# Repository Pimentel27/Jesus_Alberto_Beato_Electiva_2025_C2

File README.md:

# Jesus_Alberto_Beato_Electiva_2025_C2

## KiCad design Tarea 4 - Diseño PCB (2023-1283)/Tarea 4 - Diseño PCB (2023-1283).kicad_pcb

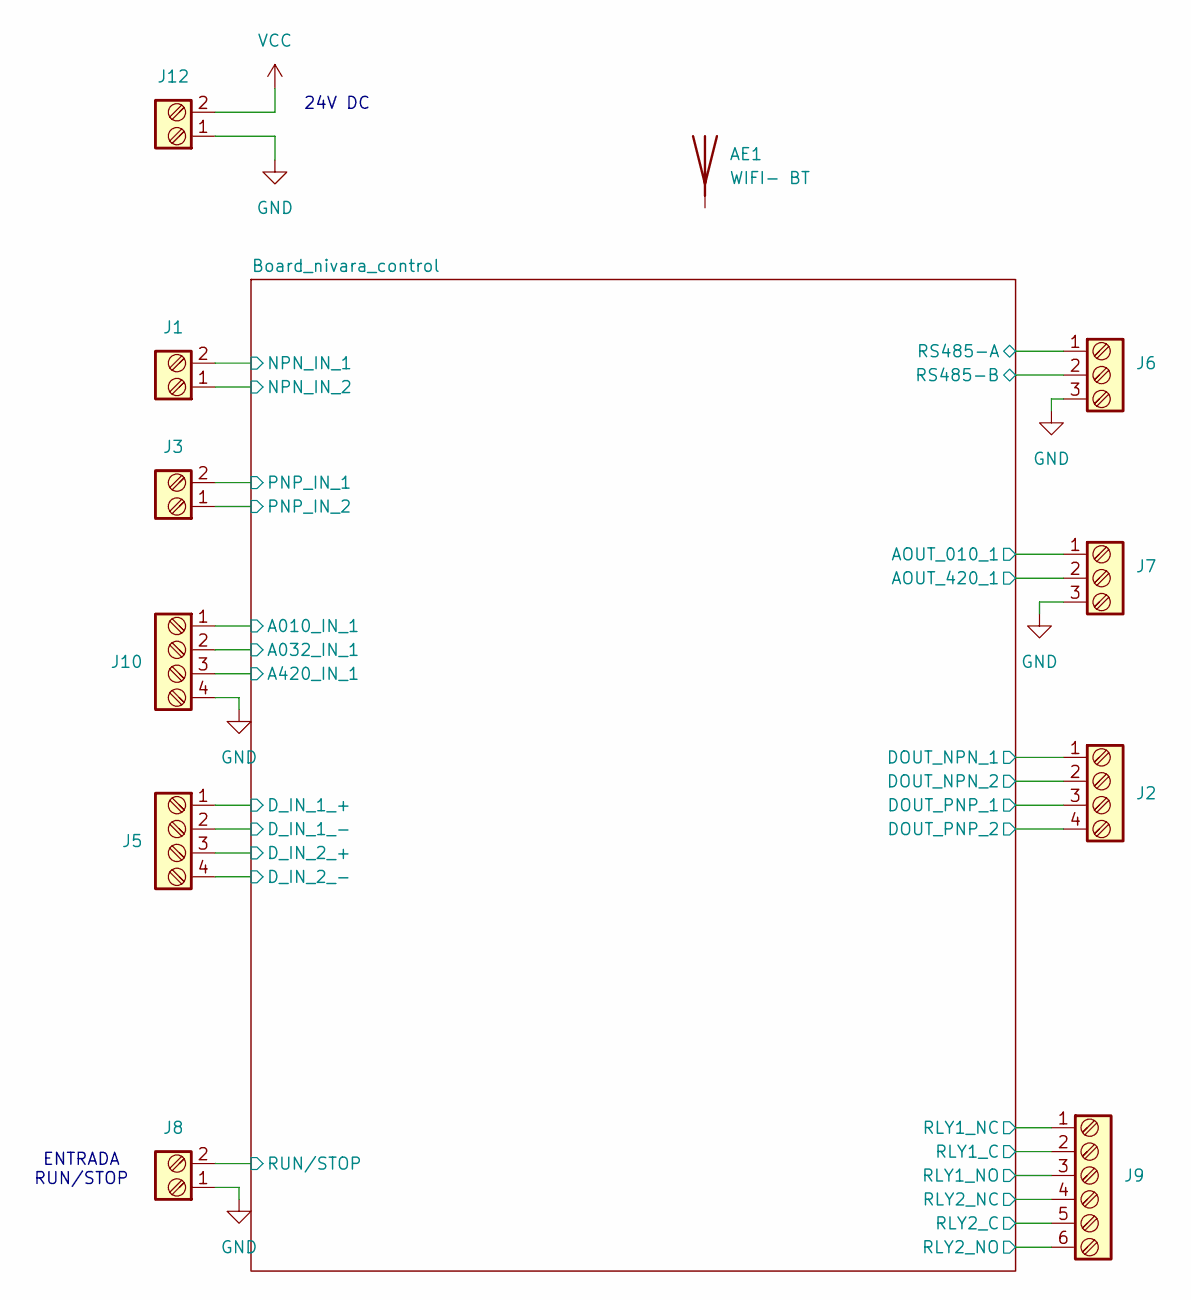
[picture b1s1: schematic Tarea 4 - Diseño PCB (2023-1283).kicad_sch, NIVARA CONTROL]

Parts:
AE1: WIFI- BT
J1, J3, J8, J12: Screw_Terminal_2_P5.00mm; TerminalBlock_Phoenix_PT-1,5-2-5.0-H_1x02_P5.00mm_Horizontal
J2, J5, J10: Screw_Terminal_4_P5.00mm; TerminalBlock_Phoenix_PT-1,5-4-5.0-H_1x04_P5.00mm_Horizontal
J6, J7: Screw_Terminal_3_P5.00mm; TerminalBlock_Phoenix_PT-1,5-3-5.0-H_1x03_P5.00mm_Horizontal
J9: Screw_Terminal_6_P5.00mm; TerminalBlock_Phoenix_PT-1,5-6-5.0-H_1x06_P5.00mm_Horizontal

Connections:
/Board_nivara_control/A010_IN_1: J10.1; also elsewhere on the board
/Board_nivara_control/A032_IN_1: J10.2; also elsewhere on the board
/Board_nivara_control/A420_IN_1: J10.3; also elsewhere on the board
/Board_nivara_control/AOUT_010_1: J7.1; also elsewhere on the board
/Board_nivara_control/AOUT_420_1: J7.2; also elsewhere on the board
/Board_nivara_control/DOUT_NPN_1: J2.1; also elsewhere on the board
/Board_nivara_control/DOUT_NPN_2: J2.2; also elsewhere on the board
/Board_nivara_control/DOUT_PNP_1: J2.3; also elsewhere on the board
/Board_nivara_control/DOUT_PNP_2: J2.4; also elsewhere on the board
/Board_nivara_control/D_IN_1_+: J5.1; also elsewhere on the board
/Board_nivara_control/D_IN_2_+: J5.3; also elsewhere on the board
/Board_nivara_control/NPN_IN_1: J1.2; also elsewhere on the board
/Board_nivara_control/NPN_IN_2: J1.1; also elsewhere on the board
/Board_nivara_control/PNP_IN_1: J3.2; also elsewhere on the board
/Board_nivara_control/PNP_IN_2: J3.1; also elsewhere on the board
/Board_nivara_control/RLY1_NC: J9.1; also elsewhere on the board
/Board_nivara_control/RLY1_NO: J9.3; also elsewhere on the board
/Board_nivara_control/RLY2_NC: J9.4; also elsewhere on the board
/Board_nivara_control/RLY2_NO: J9.6; also elsewhere on the board
/Board_nivara_control/RS485-A: J6.1; also elsewhere on the board
/Board_nivara_control/RS485-B: J6.2; also elsewhere on the board
/Board_nivara_control/RUN/STOP: J8.2; also elsewhere on the board
/RLY1_C: J9.2
/RLY2_C: J9.5
GND: J5.2, J5.4, J6.3, J7.3, J8.1, J10.4, J12.1; also elsewhere on the board
VCC: J12.2; also elsewhere on the board

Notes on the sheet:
ENTRADA RUN/STOP
24V DC

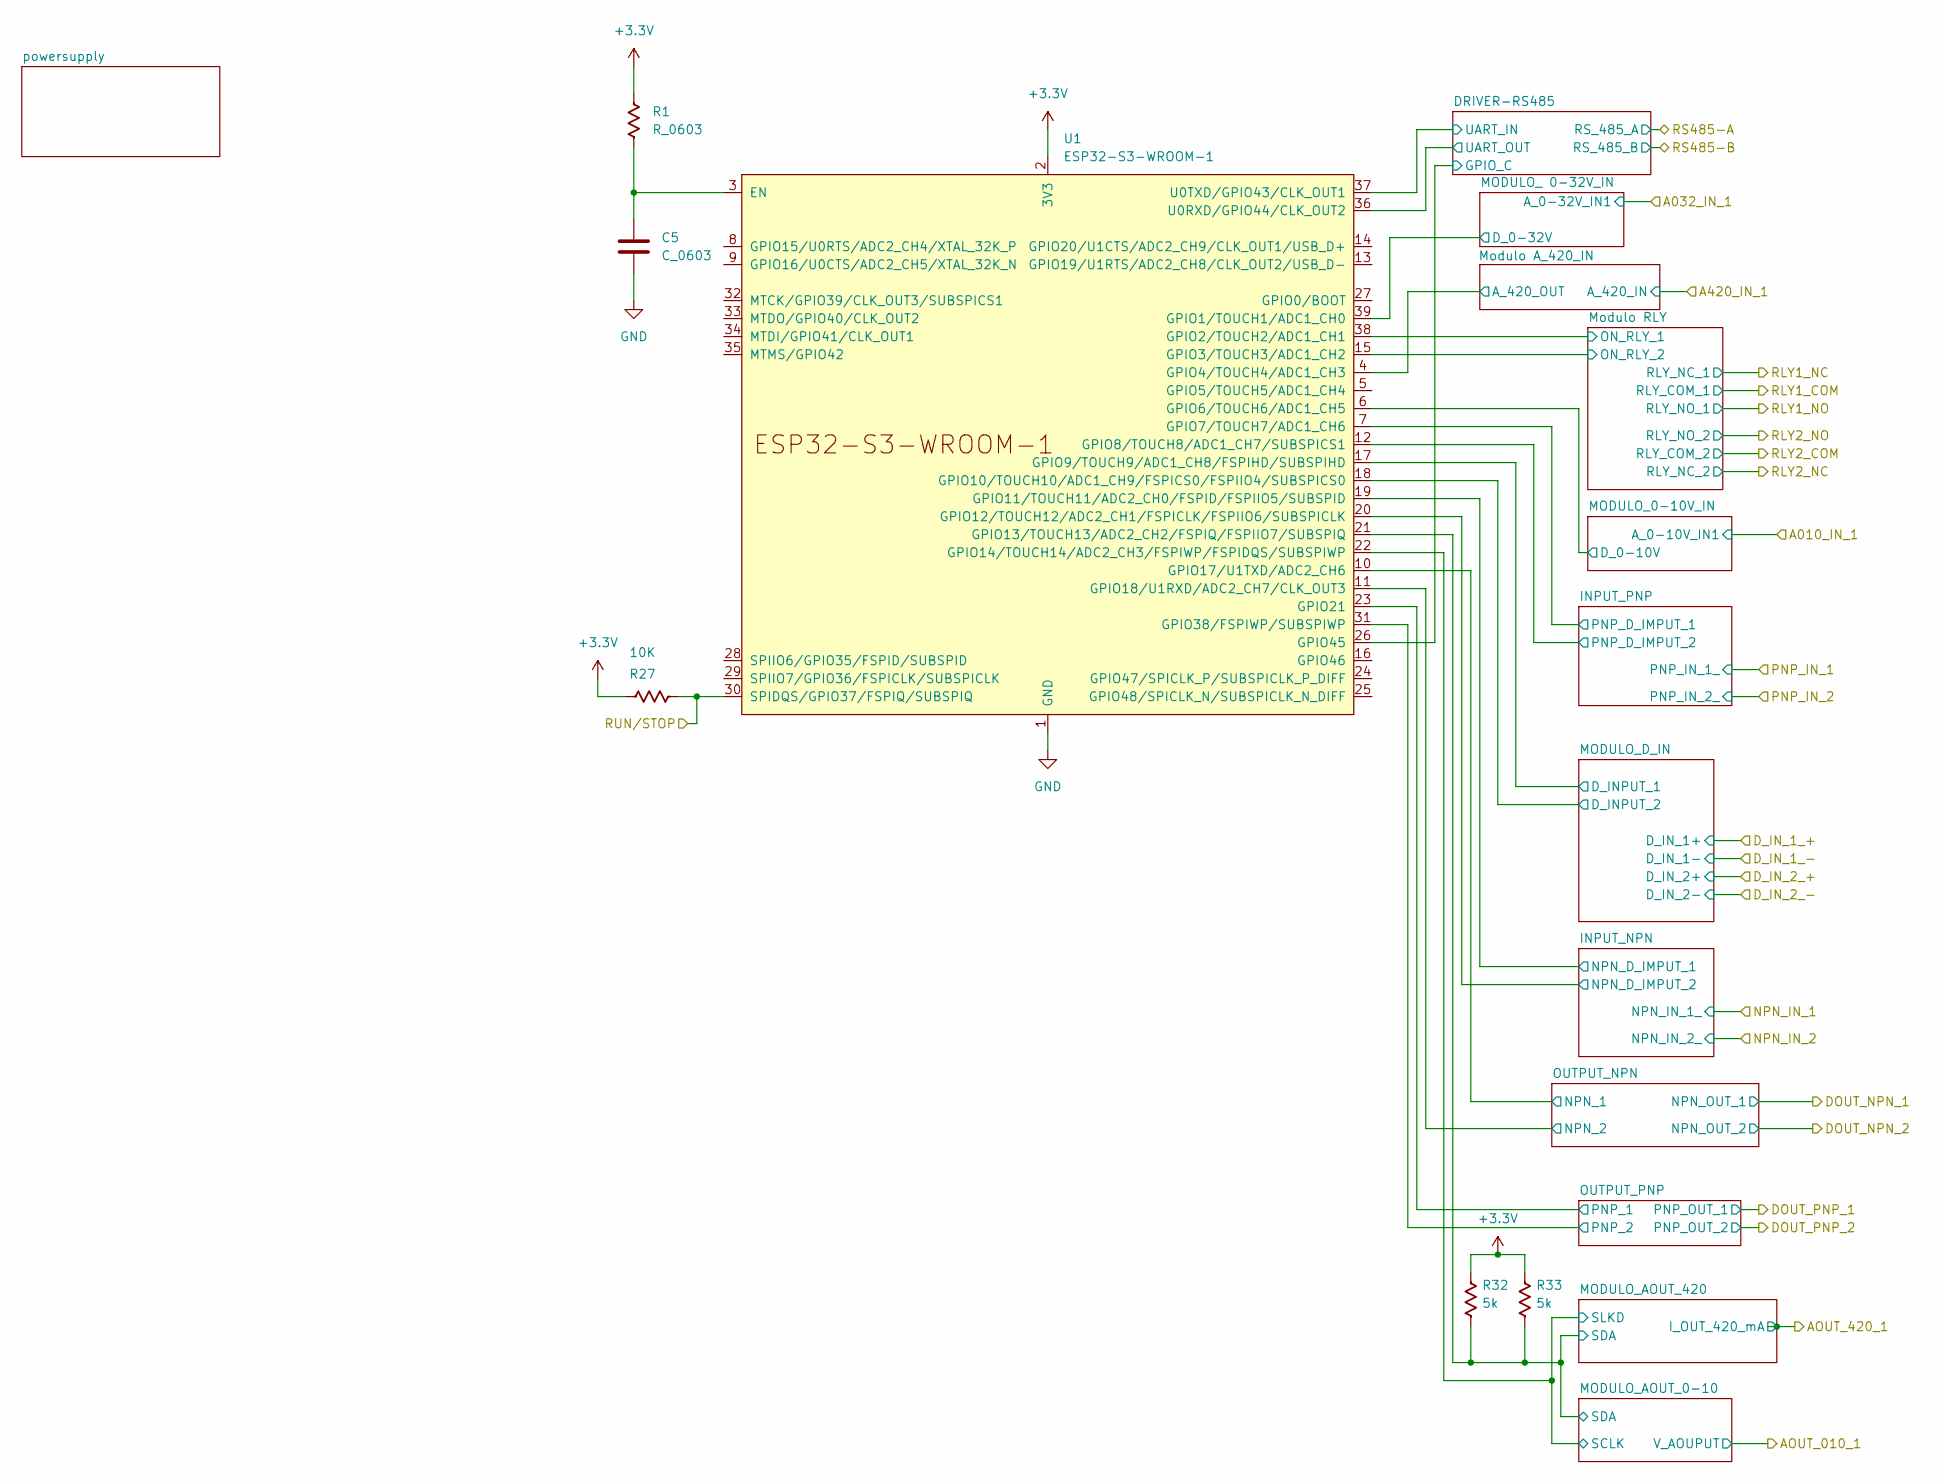
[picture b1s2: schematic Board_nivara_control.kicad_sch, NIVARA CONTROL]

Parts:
C5: C_0603; C_0603_1608Metric
R1, R27, R32, R33: R_0603; R_0603_1608Metric
U1: ESP32-S3-WROOM-1

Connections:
+3.3V: R1.1, R27.1, R32.2, R33.2, U1.2 (3V3), U1.7 (GPIO7/TOUCH7/ADC1_CH6), U1.12 (GPIO8/TOUCH8/ADC1_CH7/SUBSPICS1); also elsewhere on the board
/Board_nivara_control/A420_IN_1: U1.4 (GPIO4/TOUCH4/ADC1_CH3); also elsewhere on the board
/Board_nivara_control/DRIVER-RS485/GPIO_C: U1.26 (GPIO45); also elsewhere on the board
/Board_nivara_control/DRIVER-RS485/UART_IN: U1.37 (U0TXD/GPIO43/CLK_OUT1); also elsewhere on the board
/Board_nivara_control/DRIVER-RS485/UART_OUT: U1.36 (U0RXD/GPIO44/CLK_OUT2); also elsewhere on the board
/Board_nivara_control/INPUT_NPN/NPN_D_IMPUT_1: U1.19 (GPIO11/TOUCH11/ADC2_CH0/FSPID/FSPIIO5/S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); also elsewhere on the board
/Board_nivara_control/INPUT_NPN/NPN_D_IMPUT_2: U1.20 (GPIO12/TOUCH12/ADC2_CH1/FSPICLK/FSPIIO6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); also elsewhere on the board
/Board_nivara_control/MODULO_0-10V_IN/D_0-10V: U1.6 (GPIO6/TOUCH6/ADC1_CH5); also elsewhere on the board
/Board_nivara_control/MODULO_ 0-32V_IN/D_0-32V: U1.39 (GPIO1/TOUCH1/ADC1_CH0); also elsewhere on the board
/Board_nivara_control/MODULO_AOUT_0-10/SCLK: U1.22 (GPIO14/TOUCH14/ADC2_CH3/FSPIWP/FSPIDQS/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); also elsewhere on the board
/Board_nivara_control/MODULO_AOUT_0-10/SDA: R32.1, R33.1, U1.21 (GPIO13/TOUCH13/ADC2_CH2/FSPIQ/FSPIIO7/S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); also elsewhere on the board
/Board_nivara_control/MODULO_D_IN/D_INPUT_1: U1.17 (GPIO9/TOUCH9/ADC1_CH8/FSPIHD/SUBSPIHD); also elsewhere on the board
/Board_nivara_control/MODULO_D_IN/D_INPUT_2: U1.18 (GPIO10/TOUCH10/ADC1_CH9/FSPICS0/FSPIIO4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); also elsewhere on the board
/Board_nivara_control/Modulo RLY/ON_RLY_1: U1.38 (GPIO2/TOUCH2/ADC1_CH1); also elsewhere on the board
/Board_nivara_control/Modulo RLY/ON_RLY_2: U1.15 (GPIO3/TOUCH3/ADC1_CH2); also elsewhere on the board
/Board_nivara_control/OUTPUT_NPN/NPN_1: U1.10 (GPIO17/U1TXD/ADC2_CH6); also elsewhere on the board
/Board_nivara_control/OUTPUT_NPN/NPN_2: U1.11 (GPIO18/U1RXD/ADC2_CH7/CLK_OUT3); also elsewhere on the board
/Board_nivara_control/OUTPUT_PNP/PNP_1: U1.23 (GPIO21); also elsewhere on the board
/Board_nivara_control/OUTPUT_PNP/PNP_2: U1.31 (GPIO38/FSPIWP/SUBSPIWP); also elsewhere on the board
/Board_nivara_control/RUN/STOP: R27.2, U1.30 (SPIDQS/GPIO37/FSPIQ/SUBSPIQ); also elsewhere on the board
GND: C5.2, U1.1 (GND), U1.40 (GND), U1.41 (GND); also elsewhere on the board
unnamed: C5.1, R1.2, U1.3 (EN)

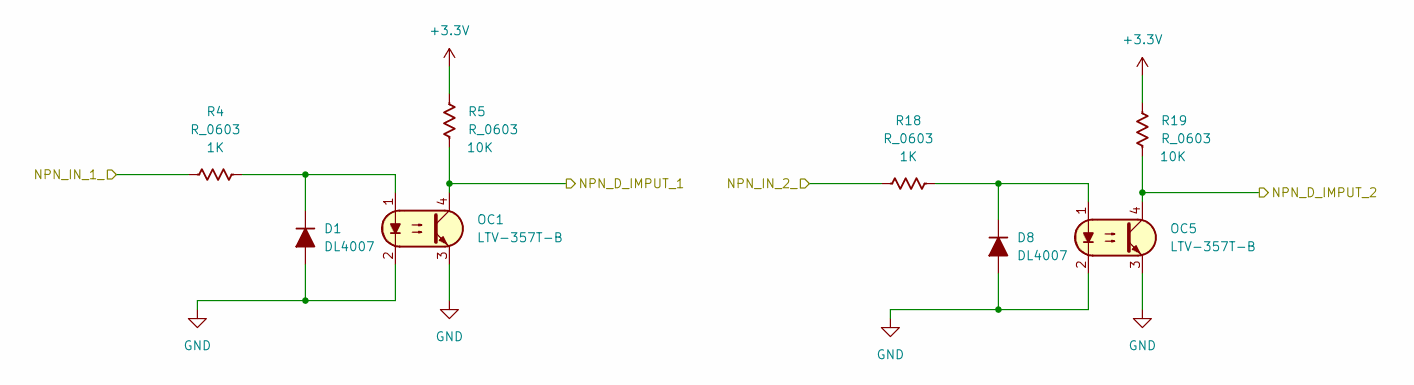
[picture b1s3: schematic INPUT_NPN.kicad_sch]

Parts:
D1, D8: DL4007; D_MELF
OC1, OC5: LTV-357T-B; SO-4_4.4x3.9mm_P2.54mm
R4, R5, R18, R19: R_0603; R_0603_1608Metric

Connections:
+3.3V: R5.2, R19.2; also elsewhere on the board
/Board_nivara_control/INPUT_NPN/NPN_D_IMPUT_1: OC1.4, R5.1; also elsewhere on the board
/Board_nivara_control/INPUT_NPN/NPN_D_IMPUT_2: OC5.4, R19.1; also elsewhere on the board
/Board_nivara_control/NPN_IN_1: R4.2; also elsewhere on the board
/Board_nivara_control/NPN_IN_2: R18.2; also elsewhere on the board
GND: D1.2 (A), D8.2 (A), OC1.2, OC1.3, OC5.2, OC5.3; also elsewhere on the board
unnamed: D1.1 (K), OC1.1, R4.1
unnamed: D8.1 (K), OC5.1, R18.1

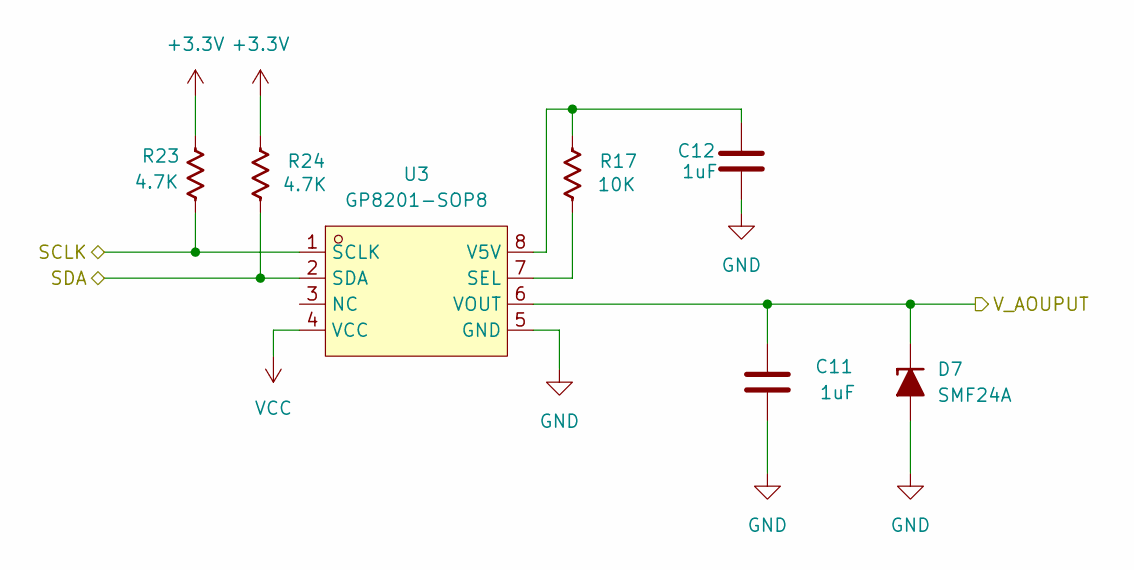
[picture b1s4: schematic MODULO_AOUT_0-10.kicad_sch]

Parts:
C11, C12: C_0805; C_0805_2012Metric
D7: SMF24A; D_SOD-123F
R17, R23, R24: R_0603; R_0603_1608Metric
U3: GP8201-SOP8; GP8201; LCSC Part C9900017396

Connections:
+3.3V: R23.2, R24.2; also elsewhere on the board
/Board_nivara_control/AOUT_010_1: C11.1, D7.1 (K), U3.6 (VOUT); also elsewhere on the board
/Board_nivara_control/MODULO_AOUT_0-10/SCLK: R23.1, U3.1 (SCLK); also elsewhere on the board
/Board_nivara_control/MODULO_AOUT_0-10/SDA: R24.1, U3.2 (SDA); also elsewhere on the board
GND: C11.2, C12.1, D7.2 (A), U3.5 (GND); also elsewhere on the board
unnamed: R17.1, U3.7 (SEL)
unnamed: C12.2, R17.2, U3.8 (V5V)
VCC: U3.4 (VCC); also elsewhere on the board

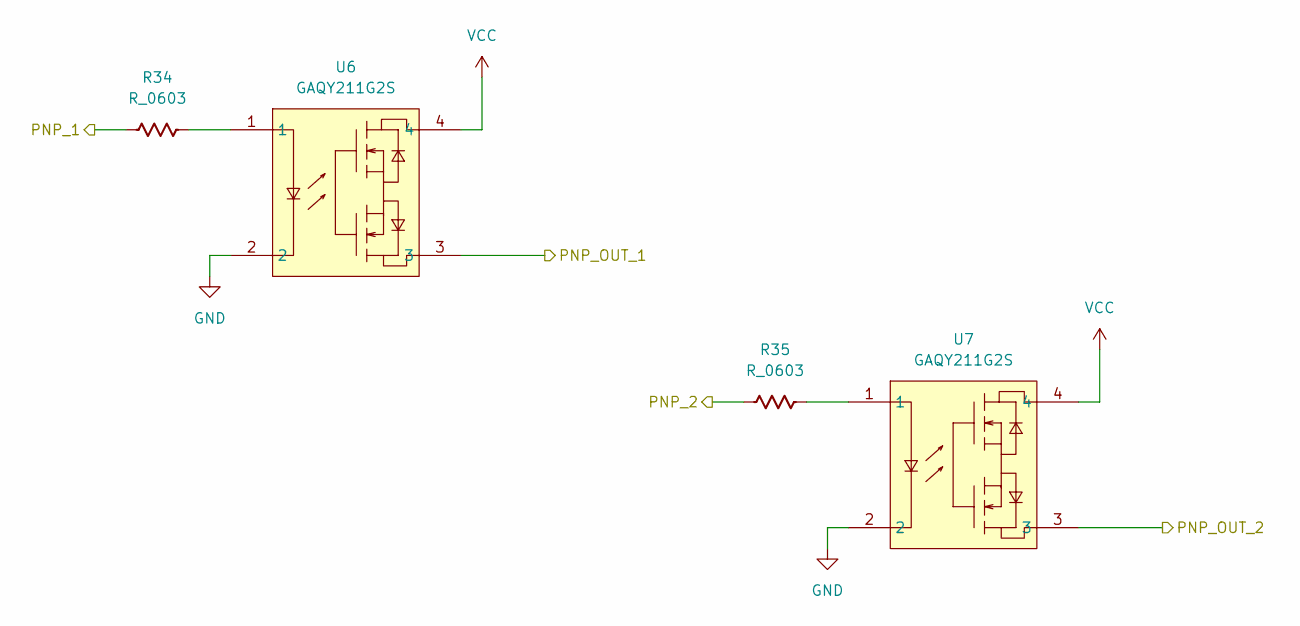
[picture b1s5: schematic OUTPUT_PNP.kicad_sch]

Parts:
R34, R35: R_0603; R_0603_1608Metric
U6, U7: GAQY211G2S; GQRLY; LCSC Part C7435104

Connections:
/Board_nivara_control/DOUT_PNP_1: U6.3; also elsewhere on the board
/Board_nivara_control/DOUT_PNP_2: U7.3; also elsewhere on the board
/Board_nivara_control/OUTPUT_PNP/PNP_1: R34.2; also elsewhere on the board
/Board_nivara_control/OUTPUT_PNP/PNP_2: R35.2; also elsewhere on the board
GND: U6.2, U7.2; also elsewhere on the board
unnamed: R34.1, U6.1
unnamed: R35.1, U7.1
VCC: U6.4, U7.4; also elsewhere on the board

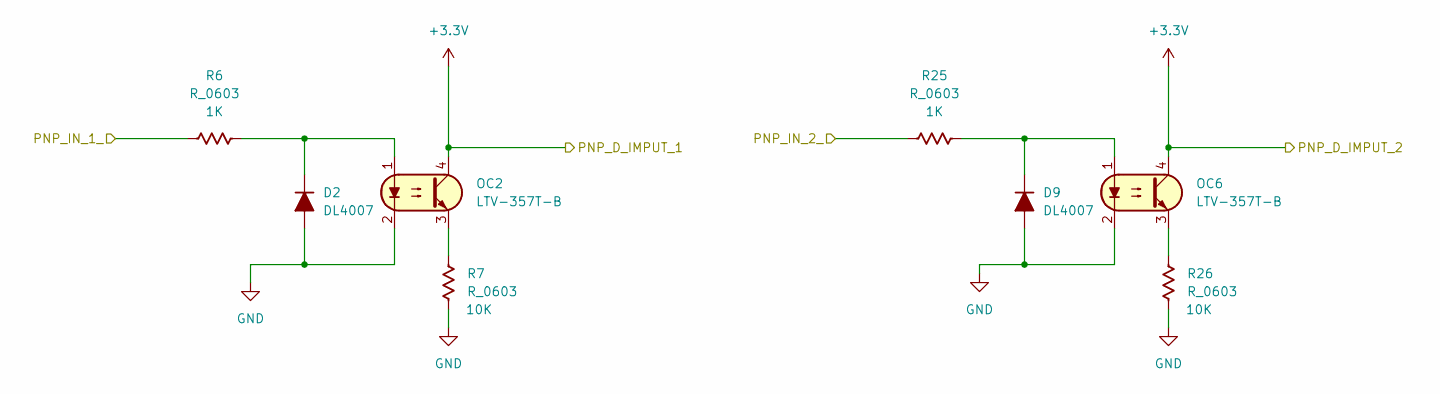
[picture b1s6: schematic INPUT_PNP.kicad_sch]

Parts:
D2, D9: DL4007; D_MELF
OC2, OC6: LTV-357T-B; SO-4_4.4x3.9mm_P2.54mm
R6, R7, R25, R26: R_0603; R_0603_1608Metric

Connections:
+3.3V: OC2.4, OC6.4; also elsewhere on the board
/Board_nivara_control/PNP_IN_1: R6.2; also elsewhere on the board
/Board_nivara_control/PNP_IN_2: R25.2; also elsewhere on the board
GND: D2.2 (A), D9.2 (A), OC2.2, OC6.2, R7.1, R26.1; also elsewhere on the board
unnamed: D2.1 (K), OC2.1, R6.1
unnamed: D9.1 (K), OC6.1, R25.1
unnamed: OC2.3, R7.2
unnamed: OC6.3, R26.2

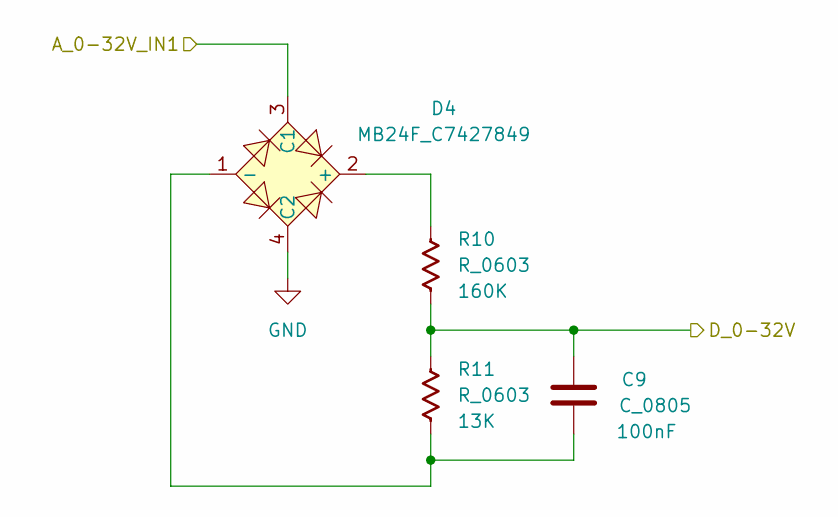
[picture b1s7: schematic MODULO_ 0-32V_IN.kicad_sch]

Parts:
C9: C_0805; C_0805_2012Metric
D4: MB24F_C7427849; MB24F; LCSC Part C7427849
R10, R11: R_0603; R_0603_1608Metric

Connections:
/Board_nivara_control/A032_IN_1: D4.3 (C1); also elsewhere on the board
/Board_nivara_control/MODULO_ 0-32V_IN/D_0-32V: C9.1, R10.1, R11.2; also elsewhere on the board
GND: D4.4 (C2); also elsewhere on the board
unnamed: D4.2 (+), R10.2
unnamed: C9.2, D4.1 (-), R11.1

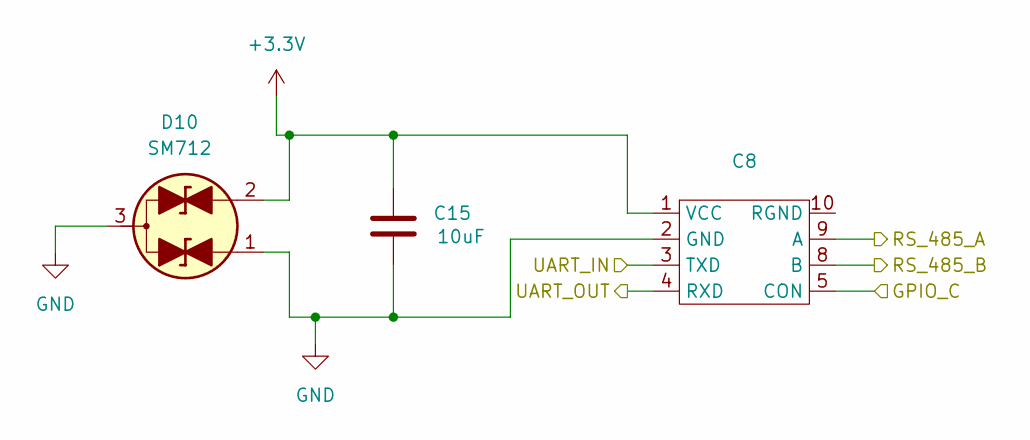
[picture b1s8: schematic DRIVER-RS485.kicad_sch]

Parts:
C8: C2992406
C15: C_0603; C_0603_1608Metric
D10: SM712; SOT-23

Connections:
+3.3V: C8.1 (VCC), C15.1, D10.2 (A2); also elsewhere on the board
/Board_nivara_control/DRIVER-RS485/GPIO_C: C8.5 (CON); also elsewhere on the board
/Board_nivara_control/DRIVER-RS485/UART_IN: C8.3 (TXD); also elsewhere on the board
/Board_nivara_control/DRIVER-RS485/UART_OUT: C8.4 (RXD); also elsewhere on the board
/Board_nivara_control/RS485-A: C8.9 (A); also elsewhere on the board
/Board_nivara_control/RS485-B: C8.8 (B); also elsewhere on the board
GND: C8.2 (GND), C15.2, D10.1 (A1), D10.3 (Com); also elsewhere on the board

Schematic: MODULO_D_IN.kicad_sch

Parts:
D5, D6: DL4007; D_MELF
OC3, OC4: LTV-357T-B; SO-4_4.4x3.9mm_P2.54mm
R13, R14, R15, R16: R_0603; R_0603_1608Metric

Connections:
+3.3V: R14.2, R16.2; also elsewhere on the board
/Board_nivara_control/D_IN_1_+: R13.2; also elsewhere on the board
/Board_nivara_control/D_IN_2_+: R15.2; also elsewhere on the board
/Board_nivara_control/MODULO_D_IN/D_INPUT_1: OC3.4, R14.1; also elsewhere on the board
/Board_nivara_control/MODULO_D_IN/D_INPUT_2: OC4.4, R16.1; also elsewhere on the board
GND: D5.2 (A), D6.2 (A), OC3.2, OC3.3, OC4.2, OC4.3; also elsewhere on the board
unnamed: D5.1 (K), OC3.1, R13.1
unnamed: D6.1 (K), OC4.1, R15.1

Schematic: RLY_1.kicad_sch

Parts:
K1, K2: SRA-24VDC-CL; RELAY-TH_SRA-X-CX; LCSC Part C127865
U5: LK1802; LCSC Part C2984831

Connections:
/Board_nivara_control/Modulo RLY/ON_RLY_1: U5.3 (1B); also elsewhere on the board
/Board_nivara_control/Modulo RLY/ON_RLY_2: U5.4 (2B); also elsewhere on the board
/Board_nivara_control/RLY1_COM: K1.5
/Board_nivara_control/RLY1_NC: K1.2; also elsewhere on the board
/Board_nivara_control/RLY1_NO: K1.1; also elsewhere on the board
/Board_nivara_control/RLY2_COM: K2.5
/Board_nivara_control/RLY2_NC: K2.2; also elsewhere on the board
/Board_nivara_control/RLY2_NO: K2.1; also elsewhere on the board
GND: U5.2 (E); also elsewhere on the board
unnamed: K1.4, U5.1 (1C)
unnamed: K2.4, U5.6 (2C)
VCC: K1.3, K2.3, U5.5 (COM); also elsewhere on the board

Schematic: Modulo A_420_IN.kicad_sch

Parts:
C10: C_0805; C_0805_2012Metric
R12: R_0603; R_0603_1608Metric

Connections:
/Board_nivara_control/A420_IN_1: C10.1, R12.2; also elsewhere on the board
GND: C10.2, R12.1; also elsewhere on the board

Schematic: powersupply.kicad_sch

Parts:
C1, C6: C_0603; C_0603_1608Metric
C2: C_1206; C_1206_3216Metric
C3, C4: C_0805; C_0805_2012Metric
JP1: SolderJumper_2_Open; SolderJumper-2_P1.3mm_Open_RoundedPad1.0x1.5mm
L1: L_Iron; L_Bourns-SRN6028
R2, R3: R_0603; R_0603_1608Metric
TP1, TP2, TP3, TP4: TestPoint; TestPoint_Bridge_Pitch2.0mm_Drill0.7mm
U2: AP63203WU; TSOT-23-6

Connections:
+3.3V: JP1.2 (B), TP2.1; also elsewhere on the board
GND: C2.2, C3.2, C4.2, R3.2, U2.4 (GND); also elsewhere on the board
unnamed: C3.1, C4.1, C6.1, JP1.1 (A), L1.2, R2.1, TP1.1
unnamed: C1.1, U2.6 (BST)
unnamed: C6.2, R2.2, R3.1, TP3.1, U2.1 (FB)
unnamed: C1.2, L1.1, U2.5 (SW)
VCC: C2.1, TP4.1, U2.2 (EN), U2.3 (IN); also elsewhere on the board

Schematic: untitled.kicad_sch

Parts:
C7: C_0805; C_0805_2012Metric
D3: MB24F_C7427849; MB24F; LCSC Part C7427849
R8, R9: R_0603; R_0603_1608Metric

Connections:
/Board_nivara_control/A010_IN_1: D3.3 (C1); also elsewhere on the board
/Board_nivara_control/MODULO_0-10V_IN/D_0-10V: C7.1, R8.1, R9.2; also elsewhere on the board
GND: D3.4 (C2); also elsewhere on the board
unnamed: D3.2 (+), R8.2
unnamed: C7.2, D3.1 (-), R9.1

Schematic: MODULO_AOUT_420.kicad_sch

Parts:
C13, C14: C_0805; C_0805_2012Metric
R20, R21, R22: R_0603; R_0603_1608Metric
U4: GP8303-TC50-EW; GP8303; LCSC Part C3445809

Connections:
+3.3V: R20.2, R21.2; also elsewhere on the board
/Board_nivara_control/AOUT_420_1: U4.8 (IOUT); also elsewhere on the board
/Board_nivara_control/MODULO_AOUT_0-10/SCLK: R21.1, U4.1 (SLCK); also elsewhere on the board
/Board_nivara_control/MODULO_AOUT_0-10/SDA: R20.1, U4.2 (SDA); also elsewhere on the board
GND: C13.2, C14.1, R22.1, U4.3 (A0), U4.4 (A1), U4.6 (GND), U4.9 (A2); also elsewhere on the board
unnamed: C14.2, R22.2, U4.7 (SET)
unnamed: C13.1, U4.10 (V5V)
VCC: U4.5 (VCC); also elsewhere on the board

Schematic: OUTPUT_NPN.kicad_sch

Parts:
R28, R36: R_0603; R_0603_1608Metric
U8, U9: GAQY211G2S; GQRLY; LCSC Part C7435104

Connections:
/Board_nivara_control/DOUT_NPN_1: U8.4; also elsewhere on the board
/Board_nivara_control/DOUT_NPN_2: U9.4; also elsewhere on the board
/Board_nivara_control/OUTPUT_NPN/NPN_1: R36.2; also elsewhere on the board
/Board_nivara_control/OUTPUT_NPN/NPN_2: R28.2; also elsewhere on the board
GND: U8.2, U8.3, U9.2, U9.3; also elsewhere on the board
unnamed: R28.1, U9.1
unnamed: R36.1, U8.1

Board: 2 copper layers, 91 parts (0 on the bottom side), 69 nets, no tracks yet.

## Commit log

2025-07-03 add files new
2025-07-16 Actualizacion
2025-07-16 New Actualizacion
2025-07-16 Complete
2025-08-22 NEW UPDATE
